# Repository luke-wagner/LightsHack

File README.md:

# LightsHack

## About

This branch is an adaptation of the main project to run on a ESP32-WROOM-32 board. The point of this project is to use a ESP32 as a dedicated controller for the lights. Buttons or joysticks controllers will later be hooked up to the board for user input and game control.

## Technologies Used

The project is using a ESP32 with MicroPython firmware installed. The project files in **device_files** are uploaded to the root of the ESP32's file system (this can be done with a tool like Thonny IDE).

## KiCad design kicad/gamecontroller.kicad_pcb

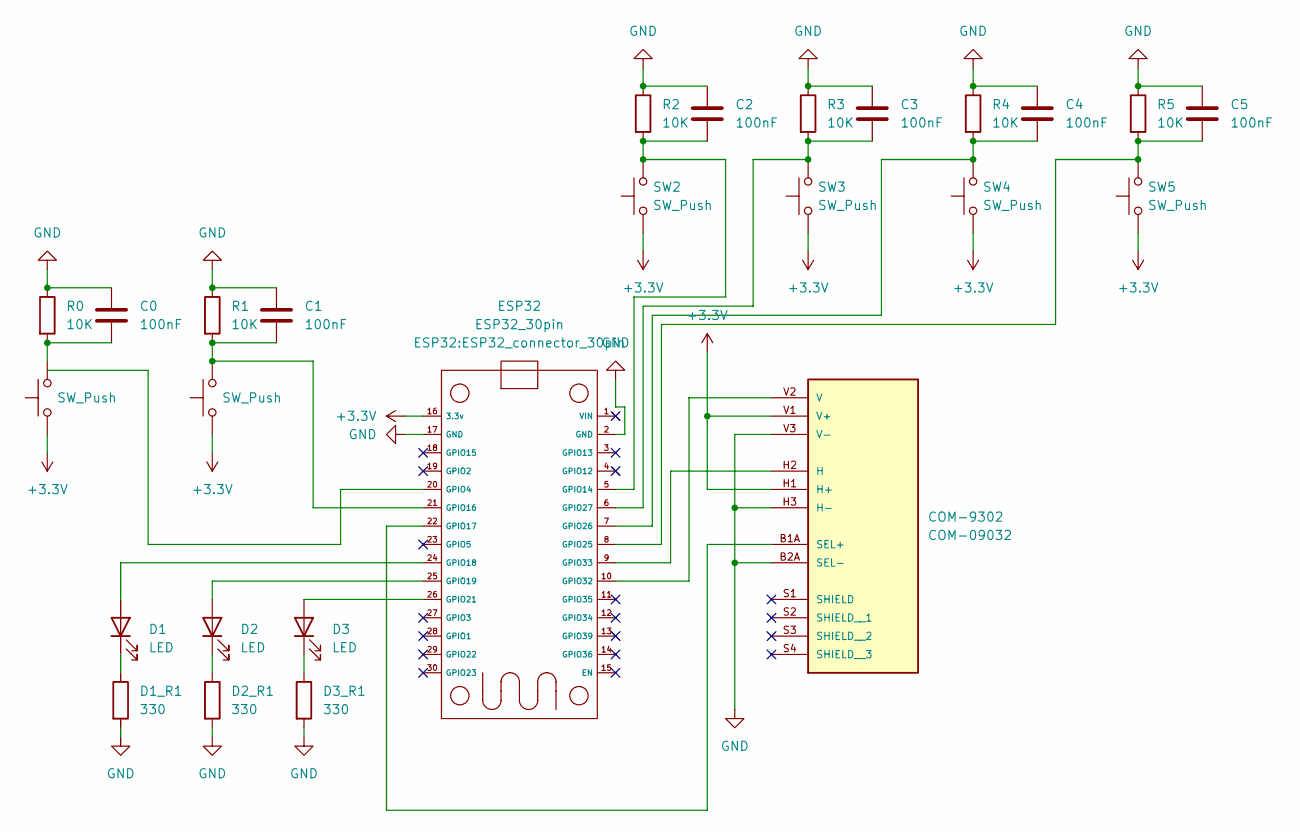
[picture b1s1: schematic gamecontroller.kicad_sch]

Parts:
C0, C1, C2, C3, C4, C5: 100nF; C_Disc_D4.3mm_W1.9mm_P5.00mm
COM-9302: COM-09032; XDCR_COM-09032; PARTREV N/A
D1, D2, D3: LED; LED_D3.0mm
D1_R1, D2_R1, D3_R1: 330; R_Axial_DIN0207_L6.3mm_D2.5mm_P7.62mm_Horizontal
ESP32: ESP32_30pin; ESP32_connector_30pin
R0, R1, R2, R3, R4, R5: 10K; R_Axial_DIN0207_L6.3mm_D2.5mm_P7.62mm_Horizontal
SW0, SW1: SW_Push; SW_PUSH_6mm
SW2, SW3, SW4, SW5: SW_Push; SW_PUSH-12mm

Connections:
+3.3V: COM-9302.H1 (H+), COM-9302.V1 (V+), ESP32.16 (3.3v), SW0.1, SW1.1, SW2.1, SW3.1, SW4.1, SW5.1
GND: C0.1, C1.1, C2.1, C3.1, C4.1, C5.1, COM-9302.B2A (SEL-), COM-9302.H3 (H-), COM-9302.V3 (V-), D1_R1.2, D2_R1.2, D3_R1.2, ESP32.2 (GND), ESP32.17 (GND), R0.1, R1.1, R2.1, R3.1, R4.1, R5.1
unnamed: C0.2, R0.2, SW0.2
unnamed: COM-9302.H2 (H), ESP32.9 (GPIO33)
unnamed: COM-9302.B1A (SEL+), ESP32.22 (GPIO17)
unnamed: COM-9302.V2 (V), ESP32.10 (GPIO32)
unnamed: D1.2 (A), ESP32.24 (GPIO18)
unnamed: D1.1 (K), D1_R1.1
unnamed: D2.2 (A), ESP32.25 (GPIO19)
unnamed: D2.1 (K), D2_R1.1
unnamed: D3.2 (A), ESP32.26 (GPIO21)
unnamed: D3.1 (K), D3_R1.1
unnamed: C2.2, ESP32.5 (GPIO14), R2.2, SW2.2
unnamed: C1.2, ESP32.21 (GPIO16), R1.2, SW1.2
unnamed: C5.2, ESP32.8 (GPIO25), R5.2, SW5.2
unnamed: C4.2, ESP32.7 (GPIO26), R4.2, SW4.2
unnamed: C3.2, ESP32.6 (GPIO27), R3.2, SW3.2

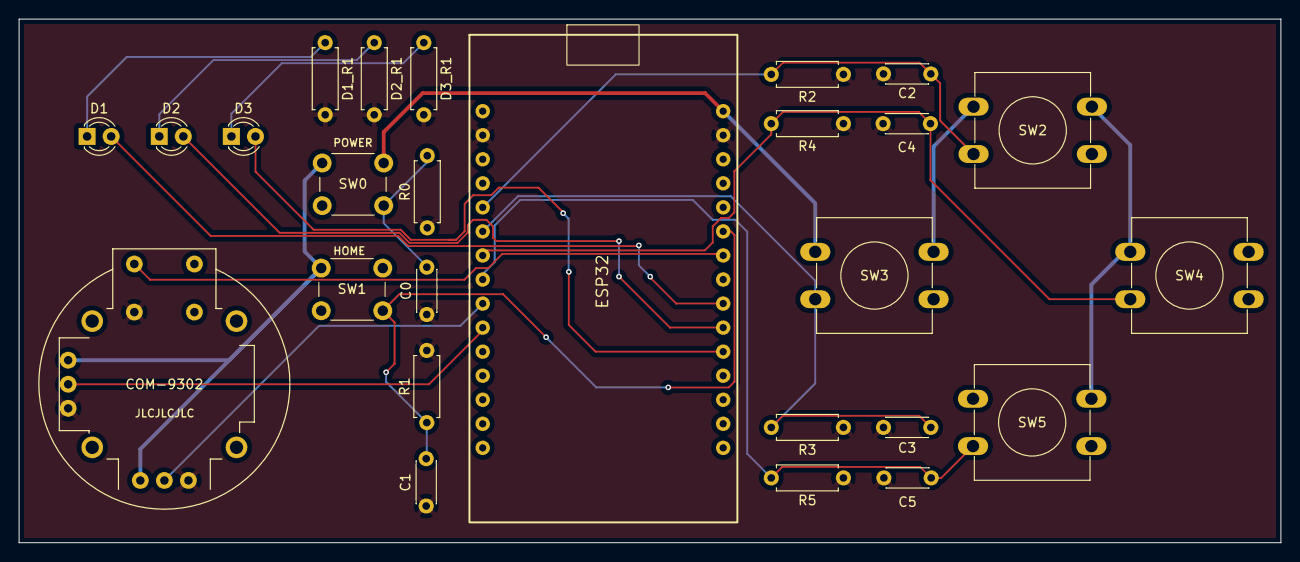
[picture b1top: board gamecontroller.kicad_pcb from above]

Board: 4 copper layers, 133.3 x 55.3 mm, 26 parts (0 on the bottom side), 17 nets.

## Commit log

2024-11-29 Add lightsimul
2024-11-29 Correct colors for simulation
2024-12-01 Add designtool
2024-12-01 Improve designtool and combine drawFramePartial and drawFrameComplete
2024-12-07 Update all local libs, make independent submodules
2024-12-07 Add submodules
2024-12-07 Add custom build tasks
2024-12-07 Add config template
2025-02-02 Initial commit for esp32 branch
2025-02-02 Modify config template and add aioble library, necessary for running program on ESP32 devices
2025-02-02 Restructure project directory
2025-02-04 Add espinput submodule
2025-02-04 Modify code to use espinput
2025-02-08 Add kicad files
2025-02-08 Update espinput submodule
2025-02-09 Updates to kicad files and update espinput submodule
2025-02-09 Update submodules, fix game-breaking bug
2025-02-09 Update submodules: interrupts and continuous execution
2025-02-14 Update kicad, gerber, and spice files
2025-02-14 Update submodules to use joystick input
2025-03-07 Updates to submodules and misc changes
2025-03-07 Add game-controller files as a submodule
2025-03-07 Update game_controller submodule
2025-03-14 Update submodules and slight changes to io code
2025-03-16 Add new LEDController class for managing on-board LEDs, modify existing code to use this class.
2025-03-17 espinput.input renamed to espinput.iodefs, add function aliases for this module
